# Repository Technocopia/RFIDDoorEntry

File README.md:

# RFIDDoorEntry
Esp8266/arduino powered keycard access system.

* NodeMCU for internet connectivity.
* Atmega8 to handle reader and door solenoid.
* Shared i2c EEPROM to store card info connected to NodeMCU
* 3mm audio jack for current transformer connected to node and atmega
* 7 GPIO
* 4 MOSFET solenoid drivers
* connects to any reader that can output wiegand data (we use a hid prox reader)

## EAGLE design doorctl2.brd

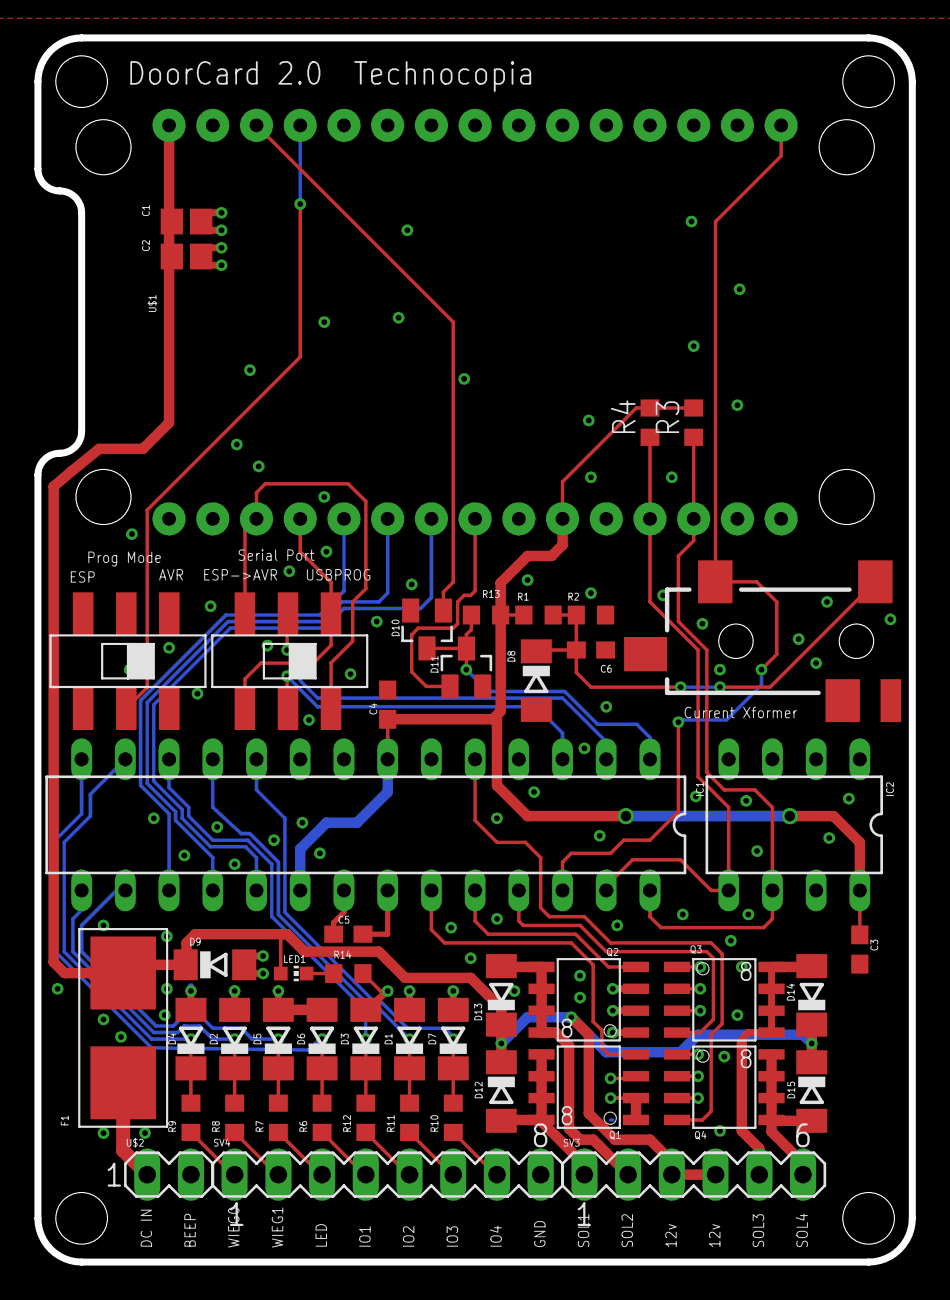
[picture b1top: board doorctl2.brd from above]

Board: 2 copper layers, 50.8 x 71.1 mm, 49 parts (0 on the bottom side), 43 nets.

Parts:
C1: 4.7uF; C0805
C2: 1uF; C0805
C3, C4, C5: 1uF; C0603
C6: 0.1uF; C0603
D1, D2, D3, D4, D5, D6, D7, D8, D9, D12, D13, D14, D15: SOD80C
D10, D11: SOT23
F1: 0154
IC1: MEGA8-P; DIL28-3
IC2: AT24CP; DIL08
JP1: AUDIO-JACK-3.5MM-SMD
LED1: CHIP-LED0603
Q1, Q2, Q3, Q4: FDS5680; SO-8
R1, R2, R3, R4, R13: 10k; R0603
R6, R7, R8, R9, R10, R11, R12: 33; R0603
R14: 330; R0603
SV3: MA06-1
SV4: MA08-1
SW1, SW2: L202011MS02Q; SMT
U$1: ESP12E_DEVKIT
U$2: MA02-1

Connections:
+3V3: C3.1, C4.1, IC1.7, IC1.20, IC2.8, R1.2, R3.2, R4.2, R13.2, U$1.3V3@0, U$1.3V3@1, U$1.3V3@2
+12V: C1.1, C2.1, D9.C, D12.C, D13.C, D14.C, D15.C, F1.2, LED1.A, SV3.3, SV3.4, U$1.VIN
AVR_RST: D10.3, D11.3, IC1.1, R13.1
CURR: IC1.26, JP1.TIP, U$1.AD0
ESP_EN: SW1.A, U$1.EN
ESP_RST: D10.1, U$1.RST
ESP_RX: SW2.A1, SW2.B2, U$1.RX
ESP_TX: SW2.A2, SW2.B1, U$1.TX
GND: C1.2, C2.2, C3.2, C4.2, C5.2, C6.1, D1.A, D2.A, D3.A, D4.A, D5.A, D6.A, D7.A, D8.A, D9.A, IC1.8, IC1.22, IC2.1, IC2.2, IC2.3, IC2.4, Q1.1, Q1.2, Q1.3, Q2.1, Q2.2, Q2.3, Q3.1, Q3.2, Q3.3, Q4.1, Q4.2, Q4.3, R2.1, R14.2, SV4.8, SW1.A2, U$1.GND@1, U$1.GND@2, U$1.GND@3, U$2.2
I0: D6.C, IC1.14, R6.2
I1: D5.C, IC1.16, R7.2
I2: D2.C, IC1.15, R8.2
I3: D4.C, IC1.13, R9.2
I5: D7.C, IC1.10, R10.2
I6: D1.C, IC1.11, R11.2
I7: D3.C, IC1.12, R12.2
L0N: D12.A, Q1.5, Q1.6, Q1.7, Q1.8, SV3.1
L0NS: IC1.23, Q1.4
L1N: D13.A, Q2.5, Q2.6, Q2.7, Q2.8, SV3.2
L1NS: IC1.24, Q2.4
L2N: D14.A, Q3.5, Q3.6, Q3.7, Q3.8, SV3.5
L2NS: IC1.25, Q3.4
L3N: D15.A, Q4.5, Q4.6, Q4.7, Q4.8, SV3.6
L3NS: IC1.5, Q4.4
MISO: IC1.18, U$1.D7
MOSI: IC1.17, U$1.D8
unnamed: R6.1, SV4.4
unnamed: R7.1, SV4.3
unnamed: R8.1, SV4.2
unnamed: R9.1, SV4.1
unnamed: C6.2, D8.C, JP1.SLEEVE, R1.1, R2.2
unnamed: R10.1, SV4.7
unnamed: R11.1, SV4.6
unnamed: R12.1, SV4.5
unnamed: F1.1, U$2.1
unnamed: C5.1, IC1.21
unnamed: LED1.C, R14.1
RX: IC1.2, SW2.B
SCK: IC1.19, U$1.D6
SCL: IC1.28, IC2.6, R3.1, U$1.D2
SDA: IC1.27, IC2.5, R4.1, U$1.D3
SW_RESET: D11.1, U$1.D5
TX: IC1.3, SW2.A

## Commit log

2016-12-02 PCB done
2016-12-02 board img
2016-12-02 Added Zener to sense xformer input
2016-12-03 cleaned iup schem, added zener
2016-12-03 Schem png

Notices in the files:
parts and their libraries:
SparkFun-Connectors: Licensing: Creative Commons ShareAlike 4.0 International - https://creativecommons.org/licenses/by-sa/4.0
